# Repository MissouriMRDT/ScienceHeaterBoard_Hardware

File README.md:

# ScienceHeater-Hardware
This repository contains the hardware files for the Science Heater project.

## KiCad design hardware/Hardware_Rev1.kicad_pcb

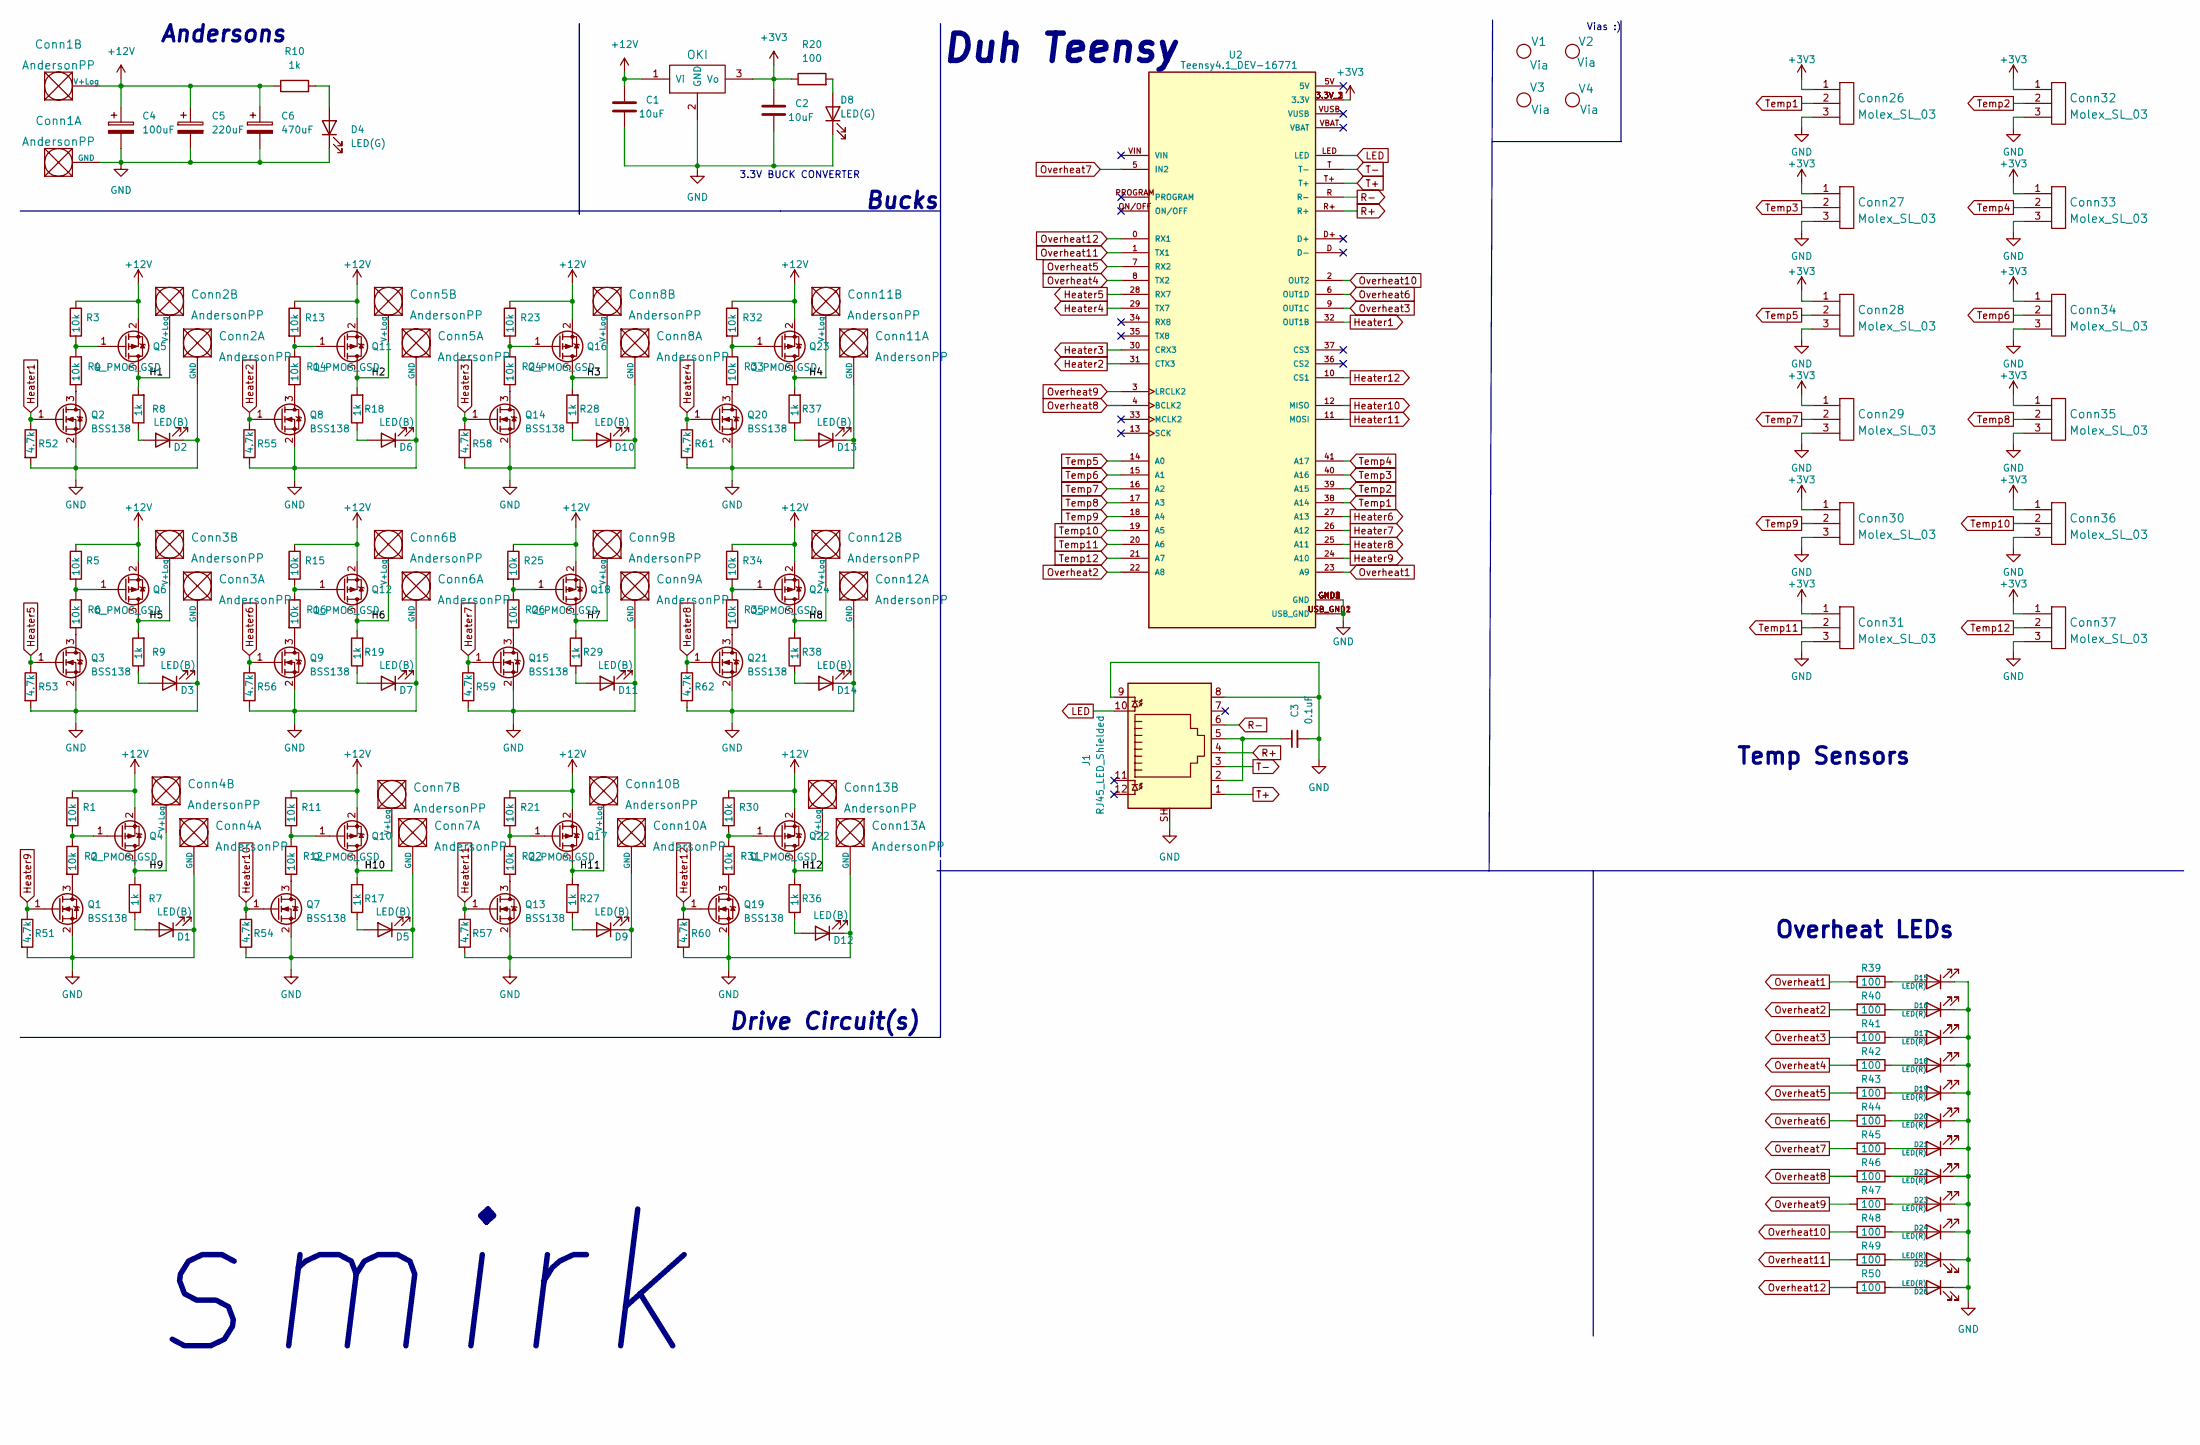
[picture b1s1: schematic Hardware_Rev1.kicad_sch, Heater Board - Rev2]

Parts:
C1, C2: 10uF; C_0603_1608Metric_Pad1.08x0.95mm_HandSolder
C3: 0.1uF; C_0603_1608Metric_Pad1.08x0.95mm_HandSolder
C4: 100uF; CP_Radial_D6.3mm_P2.50mm
C5: 220uF; CP_Radial_D6.3mm_P2.50mm
C6: 470uF; CP_Radial_D10.0mm_P2.50mm
Conn1: AndersonPP; Square_Anderson_2_H_Side_By_Side
Conn2, Conn3, Conn4, Conn5, Conn6, Conn7, Conn8, Conn9, Conn10, Conn11, Conn12, Conn13: AndersonPP; Square_Anderson_2_V_Side_By_Side
Conn26, Conn27, Conn28, Conn29, Conn30, Conn31, Conn32, Conn33, Conn34, Conn35, Conn36, Conn37: Molex_SL_03; MOLEX_SL_03_Vertical
D1, D2, D3, D5, D6, D7, D9, D10, D11, D12, D13, D14: LED(B); LED_0603_1608Metric_Pad1.05x0.95mm_HandSolder
D4, D8: LED(G); LED_0603_1608Metric_Pad1.05x0.95mm_HandSolder
D15, D16, D17, D18, D19, D20, D21, D22, D23, D24, D25, D26: LED(R); LED_0603_1608Metric_Pad1.05x0.95mm_HandSolder
J1: RJ45_LED_Shielded; RJ45_Teensy
Q1, Q2, Q3, Q7, Q8, Q9, Q13, Q14, Q15, Q19, Q20, Q21: BSS138; SOT-23
Q4, Q5, Q6, Q10, Q11, Q12, Q16, Q17, Q18, Q22, Q23, Q24: Q_PMOS_GSD; SOT-23-3
R1, R2, R3, R4, R5, R6, R11, R12, R13, R14, R15, R16, R21, R22, R23, R24, R25, R26, R30, R31, R32, R33, R34, R35: 10k; R_0603_1608Metric_Pad0.98x0.95mm_HandSolder
R7, R8, R9, R10, R17, R18, R19, R27, R28, R29, R36, R37, R38: 1k; R_0603_1608Metric_Pad0.98x0.95mm_HandSolder
R20, R39, R40, R41, R42, R43, R44, R45, R46, R47, R48, R49, R50: 100; R_0603_1608Metric_Pad0.98x0.95mm_HandSolder
R51, R52, R53, R54, R55, R56, R57, R58, R59, R60, R61, R62: 4.7k; R_0603_1608Metric_Pad0.98x0.95mm_HandSolder
U1: OKI; OKI_Horizontal
U2: Teensy4.1_DEV-16771; Teensy_4_1_Ethernet; PARTREV 4.1
V1, V2, V3, V4: Via; 4_40_Hole_Corner

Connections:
+3V3: C2.1, Conn26.1, Conn27.1, Conn28.1, Conn29.1, Conn30.1, Conn31.1, Conn32.1, Conn33.1, Conn34.1, Conn35.1, Conn36.1, Conn37.1, R20.1, U1.3 (Vo), U2.3.3V_1 (3.3V), U2.3.3V_2 (3.3V), U2.3.3V_3 (3.3V)
+12V: C1.1, C4.1, C5.1, C6.1, Conn1.2 (V+Log), Q4.2 (S), Q5.2 (S), Q6.2 (S), Q10.2 (S), Q11.2 (S), Q12.2 (S), Q16.2 (S), Q17.2 (S), Q18.2 (S), Q22.2 (S), Q23.2 (S), Q24.2 (S), R1.1, R3.1, R5.1, R10.1, R11.1, R13.1, R15.1, R21.1, R23.1, R25.1, R30.1, R32.1, R34.1, U1.1 (Vi)
/H1: Conn2.2 (V+Log), Q5.3 (D), R8.2
/H2: Conn5.2 (V+Log), Q11.3 (D), R18.2
/H3: Conn8.2 (V+Log), Q16.3 (D), R28.2
/H4: Conn11.2 (V+Log), Q23.3 (D), R37.2
/H5: Conn3.2 (V+Log), Q6.3 (D), R9.2
/H6: Conn6.2 (V+Log), Q12.3 (D), R19.2
/H7: Conn9.2 (V+Log), Q18.3 (D), R29.2
/H8: Conn12.2 (V+Log), Q24.3 (D), R38.2
/H9: Conn4.2 (V+Log), Q4.3 (D), R7.2
/H10: Conn7.2 (V+Log), Q10.3 (D), R17.2
/H11: Conn10.2 (V+Log), Q17.3 (D), R27.2
/H12: Conn13.2 (V+Log), Q22.3 (D), R36.2
GND: C1.2, C2.2, C3.2, C4.2, C5.2, C6.2, Conn1.1 (GND), Conn2.1 (GND), Conn3.1 (GND), Conn4.1 (GND), Conn5.1 (GND), Conn6.1 (GND), Conn7.1 (GND), Conn8.1 (GND), Conn9.1 (GND), Conn10.1 (GND), Conn11.1 (GND), Conn12.1 (GND), Conn13.1 (GND), Conn26.3, Conn27.3, Conn28.3, Conn29.3, Conn30.3, Conn31.3, Conn32.3, Conn33.3, Conn34.3, Conn35.3, Conn36.3, Conn37.3, D1.1 (K), D2.1 (K), D3.1 (K), D4.1 (K), D5.1 (K), D6.1 (K), D7.1 (K), D8.1 (K), D9.1 (K), D10.1 (K), D11.1 (K), D12.1 (K), D13.1 (K), D14.1 (K), D15.1 (K), D16.1 (K), D17.1 (K), D18.1 (K), D19.1 (K), D20.1 (K), D21.1 (K), D22.1 (K), D23.1 (K), D24.1 (K), D25.1 (K), D26.1 (K), J1.8, J1.9, J1.SH, Q1.2 (S), Q2.2 (S), Q3.2 (S), Q7.2 (S), Q8.2 (S), Q9.2 (S), Q13.2 (S), Q14.2 (S), Q15.2 (S), Q19.2 (S), Q20.2 (S), Q21.2 (S), R51.2, R52.2, R53.2, R54.2, R55.2, R56.2, R57.2, R58.2, R59.2, R60.2, R61.2, R62.2, U1.2 (GND), U2.GND1 (GND), U2.GND2 (GND), U2.GND3 (GND), U2.GND4 (GND), U2.GND5 (GND), U2.USB_GND1 (USB_GND), U2.USB_GND2 (USB_GND)
Heater1: Q2.1 (G), R52.1, U2.32 (OUT1B)
Heater2: Q8.1 (G), R55.1, U2.31 (CTX3)
Heater3: Q14.1 (G), R58.1, U2.30 (CRX3)
Heater4: Q20.1 (G), R61.1, U2.29 (TX7)
Heater5: Q3.1 (G), R53.1, U2.28 (RX7)
Heater6: Q9.1 (G), R56.1, U2.27 (A13)
Heater7: Q15.1 (G), R59.1, U2.26 (A12)
Heater8: Q21.1 (G), R62.1, U2.25 (A11)
Heater9: Q1.1 (G), R51.1, U2.24 (A10)
Heater10: Q7.1 (G), R54.1, U2.12 (MISO)
Heater11: Q13.1 (G), R57.1, U2.11 (MOSI)
Heater12: Q19.1 (G), R60.1, U2.10 (CS1)
LED: J1.10, U2.LED
unnamed: C3.1, J1.2, J1.5
unnamed: D1.2 (A), R7.1
unnamed: D2.2 (A), R8.1
unnamed: D3.2 (A), R9.1
unnamed: D4.2 (A), R10.2
unnamed: D5.2 (A), R17.1
unnamed: D6.2 (A), R18.1
unnamed: D7.2 (A), R19.1
unnamed: D8.2 (A), R20.2
unnamed: D9.2 (A), R27.1
unnamed: D10.2 (A), R28.1
unnamed: D11.2 (A), R29.1
unnamed: D12.2 (A), R36.1
unnamed: D13.2 (A), R37.1
unnamed: D14.2 (A), R38.1
unnamed: D15.2 (A), R39.1
unnamed: D16.2 (A), R40.1
unnamed: D17.2 (A), R41.1
unnamed: D18.2 (A), R42.1
unnamed: D19.2 (A), R43.1
unnamed: D20.2 (A), R44.1
unnamed: D21.2 (A), R45.1
unnamed: D22.2 (A), R46.1
unnamed: D23.2 (A), R47.1
unnamed: D24.2 (A), R48.1
unnamed: D25.2 (A), R49.1
unnamed: D26.2 (A), R50.1
unnamed: Q1.3 (D), R2.2
unnamed: Q2.3 (D), R4.2
unnamed: Q3.3 (D), R6.2
unnamed: Q4.1 (G), R1.2, R2.1
unnamed: Q5.1 (G), R3.2, R4.1
unnamed: Q6.1 (G), R5.2, R6.1
unnamed: Q7.3 (D), R12.2
unnamed: Q8.3 (D), R14.2
unnamed: Q9.3 (D), R16.2
unnamed: Q10.1 (G), R11.2, R12.1
unnamed: Q11.1 (G), R13.2, R14.1
unnamed: Q12.1 (G), R15.2, R16.1
unnamed: Q13.3 (D), R22.2
unnamed: Q14.3 (D), R24.2
unnamed: Q15.3 (D), R26.2
unnamed: Q16.1 (G), R23.2, R24.1
unnamed: Q17.1 (G), R21.2, R22.1
unnamed: Q18.1 (G), R25.2, R26.1
unnamed: Q19.3 (D), R31.2
unnamed: Q20.3 (D), R33.2
unnamed: Q21.3 (D), R35.2
unnamed: Q22.1 (G), R30.2, R31.1
unnamed: Q23.1 (G), R32.2, R33.1
unnamed: Q24.1 (G), R34.2, R35.1
Overheat1: R39.2, U2.23 (A9)
Overheat2: R40.2, U2.22 (A8)
Overheat3: R41.2, U2.9 (OUT1C)
Overheat4: R42.2, U2.8 (TX2)
Overheat5: R43.2, U2.7 (RX2)
Overheat6: R44.2, U2.6 (OUT1D)
Overheat7: R45.2, U2.5 (IN2)
Overheat8: R46.2, U2.4 (BCLK2)
Overheat9: R47.2, U2.3 (LRCLK2)
Overheat10: R48.2, U2.2 (OUT2)
Overheat11: R49.2, U2.1 (TX1)
Overheat12: R50.2, U2.0 (RX1)
R+: J1.4, U2.R+
R-: J1.6, U2.R (R-)
T+: J1.1, U2.T+
T-: J1.3, U2.T (T-)
Temp1: Conn26.2, U2.38 (A14)
Temp2: Conn32.2, U2.39 (A15)
Temp3: Conn27.2, U2.40 (A16)
Temp4: Conn33.2, U2.41 (A17)
Temp5: Conn28.2, U2.14 (A0)
Temp6: Conn34.2, U2.15 (A1)
Temp7: Conn29.2, U2.16 (A2)
Temp8: Conn35.2, U2.17 (A3)
Temp9: Conn30.2, U2.18 (A4)
Temp10: Conn36.2, U2.19 (A5)
Temp11: Conn31.2, U2.20 (A6)
Temp12: Conn37.2, U2.21 (A7)

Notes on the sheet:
Drive Circuit(s)
Temp Sensors
Duh Teensy
Andersons
3.3V BUCK CONVERTER
Bucks
Vias :)
Overheat LEDs
smirk

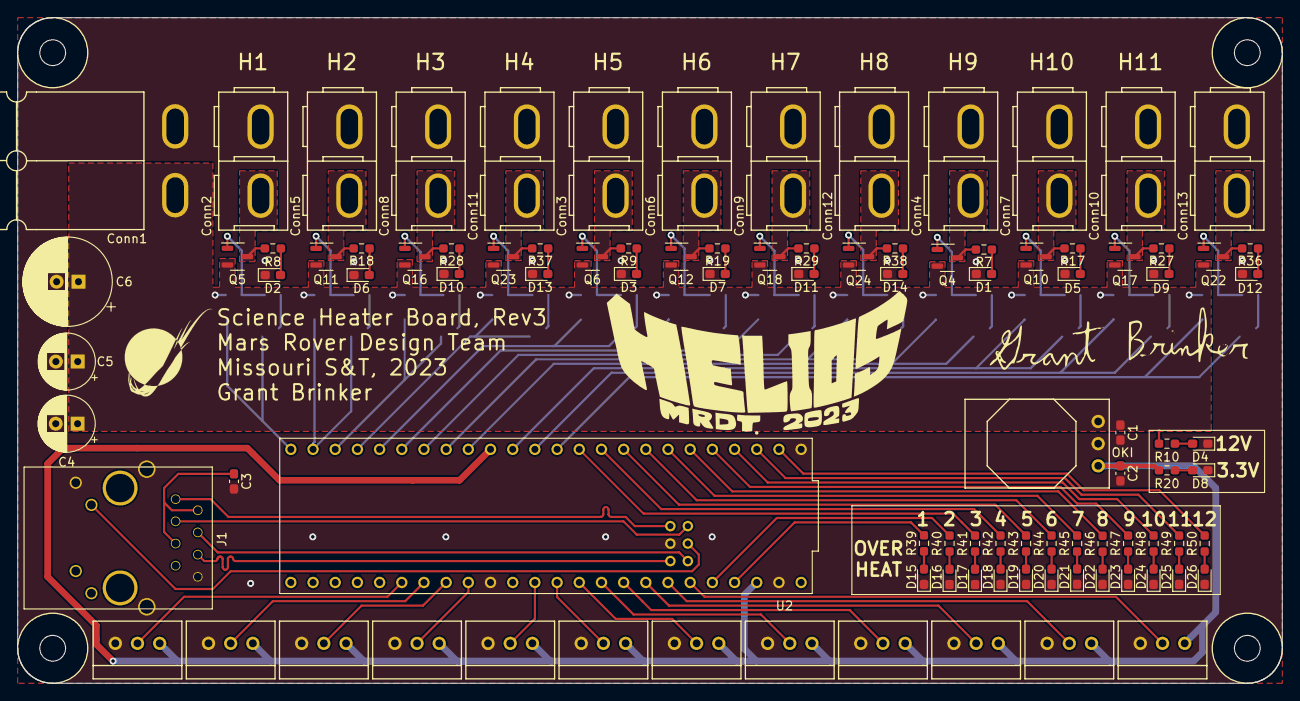
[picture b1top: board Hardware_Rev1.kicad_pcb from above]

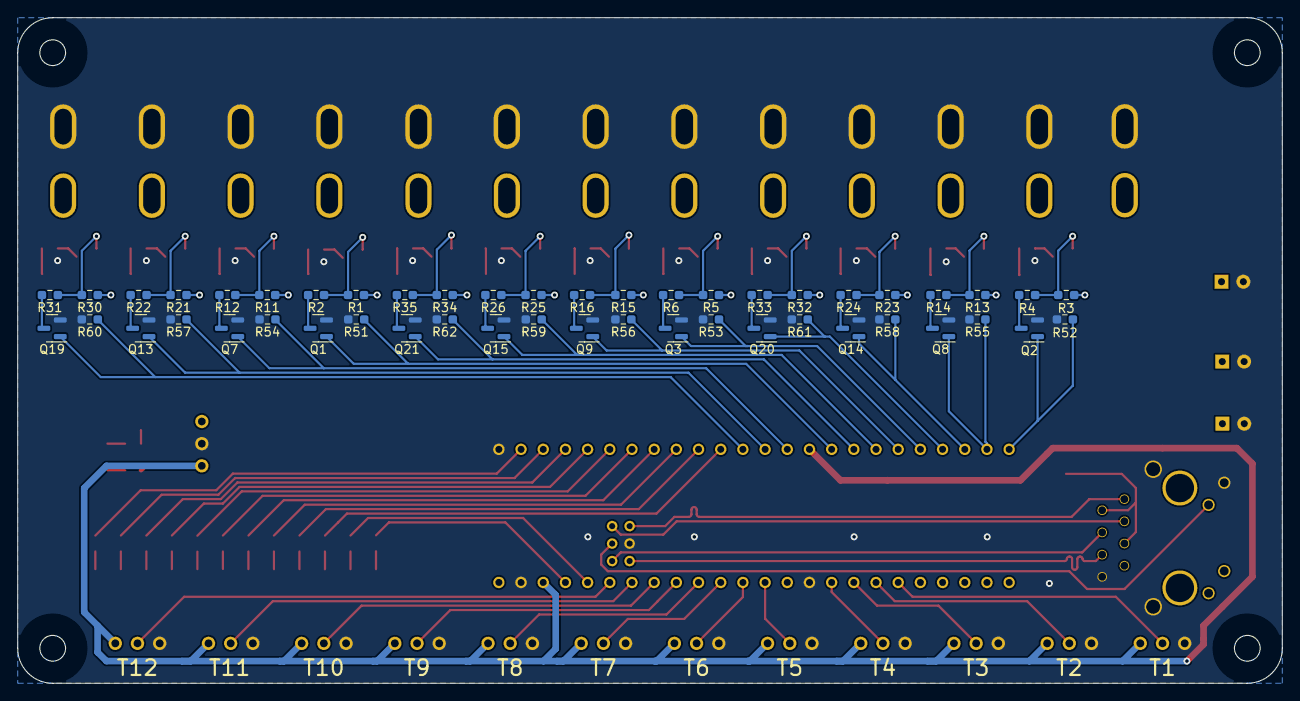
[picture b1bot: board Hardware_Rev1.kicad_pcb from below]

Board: 2 copper layers, 144.8 x 76.2 mm, 150 parts (48 on the bottom side), 105 nets.

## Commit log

2021-09-24 Added andersons for PV and ground
2021-09-24 Added Placeholders
    Added Capacitor bank placeholder and Thermistor measurement placeholder.
2021-09-28 Worked on mosfet driver
2021-10-02 Added mosfet
    Went with BUK7M33-60EX with 60V and 24A. May need to switch this out with a different amperage
2021-10-02 Added teensy to board and planned wire connections
2021-10-02 Added thermistor measurement system
2021-10-06 Added buck convertors, labeled components, and added resistance and capacitance values
2021-10-08 Added Current Limiter and Removed example
    Gave Rmin for Thermistor and removed Comparative Resistance Circuit example
2021-10-11 Board Review
    Thermistor moved
    Edit Ethernet
    Find nichrome wire to be used before PDR
2021-10-12 Cleaned up ethernet circuit wiring
2021-10-15 Fixed ethernet circuit and general cleaning
2021-10-16 Nichrome Cleanup
    Cleaned up circuit for PDR and assigned R for wire
2021-10-30 Notated and reorganized schematic
    Removed measurement resistor in gate driver circuit, removed thermistor to replace with a different sensor, and wrote a note on the Andersons
2021-11-02 Applied footprints to capacitors
2021-11-03 Assigned footprints and started layout
2021-11-06 Changed PV to 12V and added TH OpAmp circuit
2021-11-07 Added capacitor bank
2021-11-07 Adjusted opamp circuit
2021-11-08 Footprints and layout work
2021-11-08 Added more mosfets and sensors
2021-11-08 Capbank and breakout thermistor
    Redid the capacitor bank and added a copy of the sheet with thermistors so we can change to other sensors for now. Also made some aesthetic changes.
2021-11-08 Updated Andersons and layout
2021-11-09 Arranged components on layout
2021-11-12 Added ground and traces
2021-11-13 Worked on layout
2021-11-14 Finished layout?
2021-11-16 Increased trace sizes
2021-11-16 Created BOM
2021-11-17 CDR Changes
2021-11-17 Made step files
2021-11-17 Step files
2021-11-19 Changed power plane priority
2021-11-20 Un-garbaged RJ45 layout
2021-11-20 Added labels to layout
2021-11-20 Changed label layers
2021-11-20 Made Gerb files
2021-12-08 generated .STEP file
2021-12-30 Fixed rescue library
2022-03-05 Initial Rev2 Design
2022-03-05 Adjusted heating block connections
2022-03-08 Fixed Mosfet LEDs
2022-03-08 Added mounting holes
2022-03-11 Generated Rev2 BOM
2022-03-15 Generated Gerbs (hopefully)
2022-03-19 moved uF connects. generated gerbs
2022-03-19 same as previous
2022-09-07 Rev1 file made
2022-09-07 some title stuff
2022-09-08 finished buck converters and andersons
2022-09-13 finished schematic (still need BOM and footprint assignments)
2022-09-13 final touches
2022-09-20 finished assigning footprints
2022-09-20 BOM created?
2022-09-23 schematic review :)
2022-09-23 schematic review part 2
2022-10-06 layout soon?
2022-10-07 Finished Schematic, kinda finished BOM, layout tomorrow.
2022-10-10 Started Layout + Added Vias
2022-10-11 mmm mosfets are good now!
2022-10-11 updated layout with drill holes (they don't fit??)
2022-10-18 Worked on Layout of Drivers and Bucks
2022-10-22 Fixed up tracings, starting to put everything together.
2022-10-29 updated hardware files
2022-10-29 other
2022-10-29 closing kicad
2022-10-31 only drive circuit placement left
2022-10-31 placed everything
2022-10-31 started tracing
2022-11-01 added name stuff
2022-11-02 its got a great personality
2022-11-02 it's small, but it could be smaller. just wiring now and a couple of labels.
2022-11-02 closing kicad, see previous push
2022-11-03 good progress on traces, finishing them tomorrow probably
2022-11-08 made layout changes, didn't finish everything tho
2022-11-09 maor
2022-11-10 Added Image to silkscreen
    WHAT IS MY PURPOSE
2022-11-11 Spaced Out stuff
    resistors and caps :)
2022-11-12 lots of wires
    dont roast pls
2022-12-10 the start of pain
2022-12-11 just need to copy paste 11 more drive circuits and update the teensy
2022-12-12 waht duh hek do I do for the teenser
2022-12-12 done with schematic ?
2022-12-17 Fixed schematic
2022-12-17 Placed heater block connectors
2022-12-17 Worked on connector placements
2022-12-18 Finished toggle circuits
2022-12-18 Finished connections
2022-12-18 Finished layout
2022-12-20 Fixed board header
2022-12-20 Added pull down resistors
2022-12-20 Cleaned traces
2022-12-20 Extended 12V plane
2022-12-28 Made layout review changes
2022-12-28 Generated BOM + Gerbs
2022-12-28 Changed teensy footprint
2022-12-28 Fixed Heater 5 plane
2022-12-28 Fixed schematic mosfets
2022-12-29 Fixed mosfet circuits
2022-12-29 Moved sensor power trace
2022-12-29 Generated Gerbs
2023-01-20 made STEP file
2023-04-20 Rev2 schematic
2023-04-20 Cleaned up schematic
2023-04-20 Started layout heater ports
2023-04-20 Better heater circuit
2023-04-21 Worked on heater circuits
2023-04-21 Finished components + Traces
2023-04-21 Added Helios logo
2023-04-21 Update fp-info-cache
2023-04-22 Made gerbs
2023-04-22 renamed gerbs for documentation purposes
2023-05-07 Fixed pfet connections
2023-05-07 Fixed silkscreens + planes
